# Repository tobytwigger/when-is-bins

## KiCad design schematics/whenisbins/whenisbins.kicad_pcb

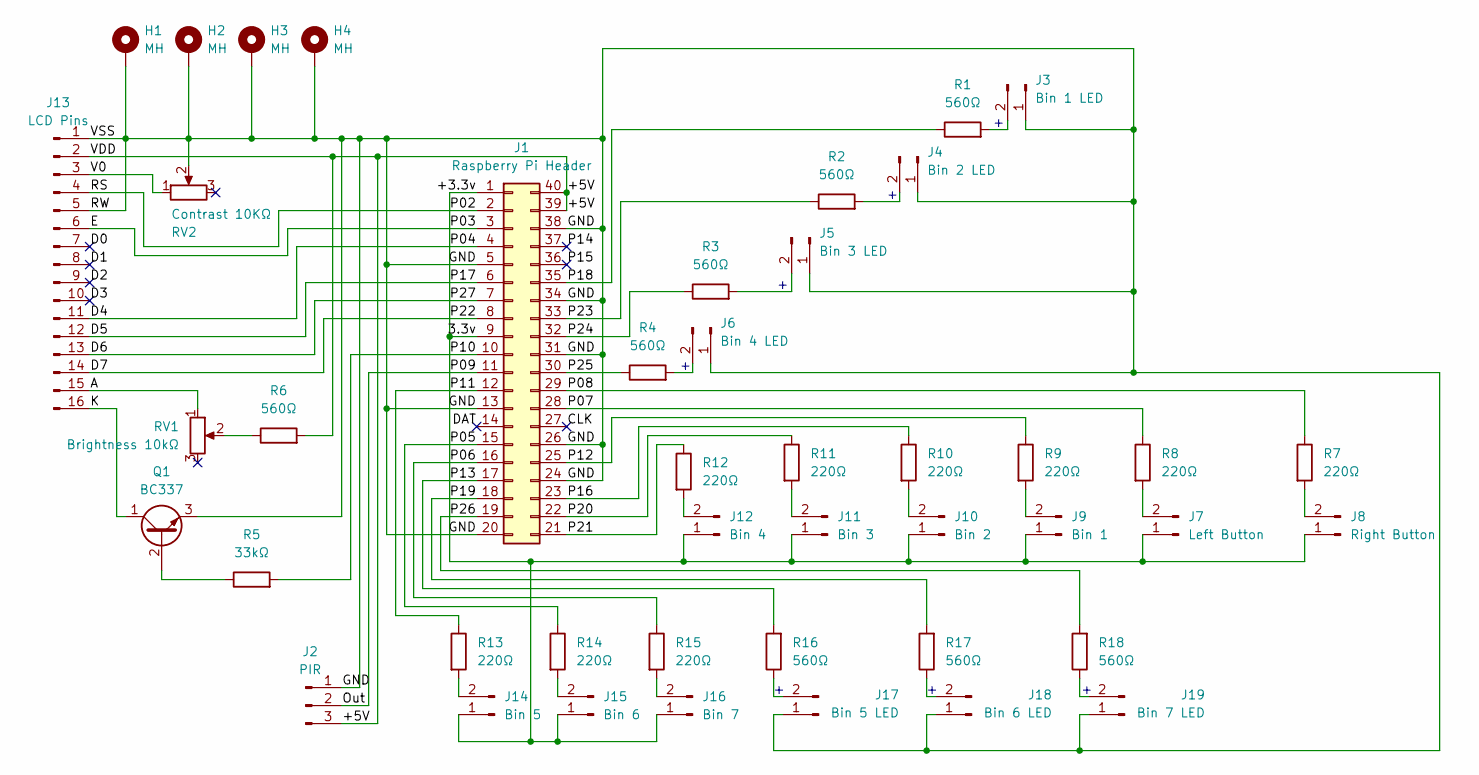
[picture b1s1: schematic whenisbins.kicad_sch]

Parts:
H1, H2, H3, H4: MH
J1: Raspberry Pi Header; PinHeader_2x20_P2.54mm_Vertical
J2: PIR; PinHeader_1x03_P2.54mm_Vertical
J3: Bin 1 LED; PinHeader_1x02_P2.54mm_Vertical
J4: Bin 2 LED; PinHeader_1x02_P2.54mm_Vertical
J5: Bin 3 LED; PinHeader_1x02_P2.54mm_Vertical
J6: Bin 4 LED; PinHeader_1x02_P2.54mm_Vertical
J7: Left Button; PinHeader_1x02_P2.54mm_Vertical
J8: Right Button; PinHeader_1x02_P2.54mm_Vertical
J9: Bin 1; PinHeader_1x02_P2.54mm_Vertical
J10: Bin 2; PinHeader_1x02_P2.54mm_Vertical
J11: Bin 3; PinHeader_1x02_P2.54mm_Vertical
J12: Bin 4; PinHeader_1x02_P2.54mm_Vertical
J13: LCD Pins; PinSocket_1x16_P2.54mm_Horizontal
J14: Bin 5; PinHeader_1x02_P2.54mm_Vertical
J15: Bin 6; PinHeader_1x02_P2.54mm_Vertical
J16: Bin 7; PinHeader_1x02_P2.54mm_Vertical
J17: Bin 5 LED; PinHeader_1x02_P2.54mm_Vertical
J18: Bin 6 LED; PinHeader_1x02_P2.54mm_Vertical
J19: Bin 7 LED; PinHeader_1x02_P2.54mm_Vertical
Q1: BC337; TO-92_Inline
R1, R2, R3, R4, R6, R16, R17, R18: 560Ω; R_Axial_DIN0207_L6.3mm_D2.5mm_P10.16mm_Horizontal
R5: 33kΩ; R_Axial_DIN0207_L6.3mm_D2.5mm_P10.16mm_Horizontal
R7, R8, R9, R10, R11, R12, R13, R14, R15: 220Ω; R_Axial_DIN0207_L6.3mm_D2.5mm_P10.16mm_Horizontal
RV1: Brightness 10kΩ; Potentiometer_Runtron_RM-065_Vertical
RV2: Contrast 10KΩ; Potentiometer_Runtron_RM-065_Vertical

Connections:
/+3.3v: J1.1, J1.9, J7.1, J8.1, J9.1, J10.1, J11.1, J12.1, J14.1, J15.1, J16.1
/+5V: J1.39, J1.40, J2.3, J13.2, R6.2
/A: J13.15, RV1.1
/CLK: J1.27
/D0: J13.7
/D1: J13.8
/D2: J13.9
/D3: J13.10
/D4: J1.4, J13.11
/D5: J1.6, J13.12
/D6: J1.7, J13.13
/D7: J1.8, J13.14
/DAT: J1.14
/E: J1.3, J13.6
/GND: H1.1, H2.1, H3.1, H4.1, J1.5, J1.13, J1.20, J1.24, J1.26, J1.31, J1.34, J1.38, J2.1, J3.1, J4.1, J5.1, J6.1, J13.1, J13.5, J17.1, J18.1, J19.1, Q1.3 (E), RV2.2
/K: J13.16, Q1.1 (C)
/Out: J1.11, J2.2
/P02: J1.2, J13.4
/P05: J1.15, R14.1
/P06: J1.16, R15.1
/P07: J1.28, R8.1
/P08: J1.29, R7.1
/P10: J1.10, R5.2
/P11: J1.12, R13.1
/P12: J1.25, R9.1
/P13: J1.17, R16.2
/P14: J1.37
/P15: J1.36
/P16: J1.23, R10.1
/P18: J1.35, R1.1
/P19: J1.18, R17.2
/P20: J1.22, R11.1
/P21: J1.21, R12.1
/P23: J1.33, R2.1
/P24: J1.32, R3.1
/P25: J1.30, R4.1
/P26: J1.19, R18.2
/V0: J13.3, RV2.1
unnamed: J3.2, R1.2
unnamed: J4.2, R2.2
unnamed: J5.2, R3.2
unnamed: J6.2, R4.2
unnamed: J7.2, R8.2
unnamed: J8.2, R7.2
unnamed: J9.2, R9.2
unnamed: J10.2, R10.2
unnamed: J11.2, R11.2
unnamed: J12.2, R12.2
unnamed: J14.2, R13.2
unnamed: J15.2, R14.2
unnamed: J16.2, R15.2
unnamed: J17.2, R16.1
unnamed: J18.2, R17.1
unnamed: J19.2, R18.1
unnamed: Q1.2 (B), R5.1
unnamed: R6.1, RV1.2

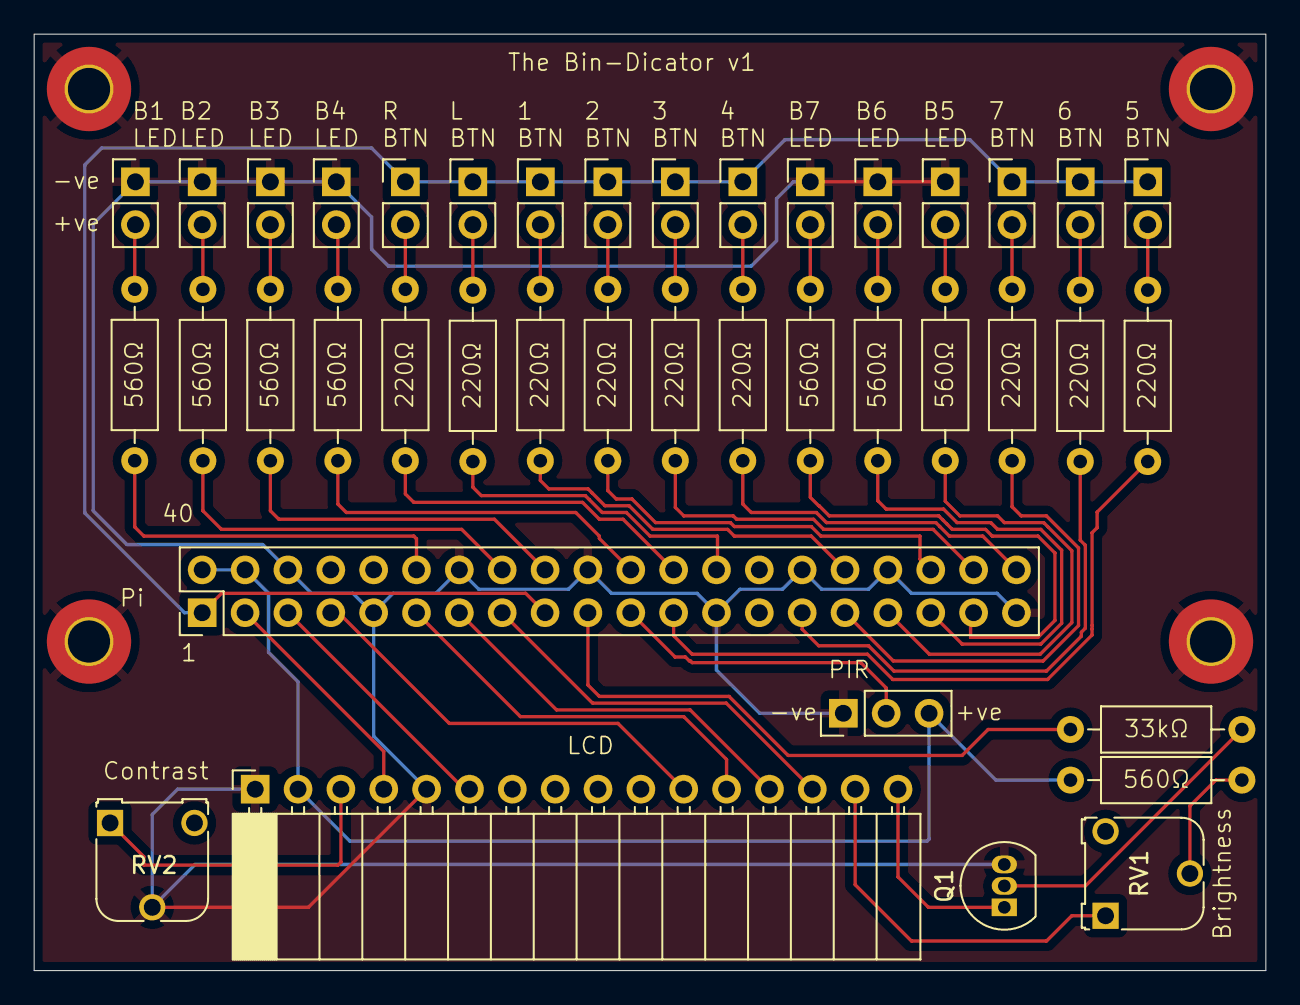
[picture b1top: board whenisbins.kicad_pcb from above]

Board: 2 copper layers, 73.0 x 55.5 mm, 44 parts (0 on the bottom side), 48 nets.

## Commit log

2025-01-06 Fixes
2025-01-07 Move database
2025-01-07 Possibly the final firmware fix
2025-01-07 Fix path used to the python script when called in node
2025-01-08 Rewrite app runner
2025-01-08 Boot on start up and config UI improvements
2025-01-09 Update PCB and electrical schematics and finalise pinouts
2025-01-09 Fix ui issue
2025-01-09 Support more councils
2025-01-09 Minor firmware updates
2025-01-10 Finalise pcb and set up selenium
2025-01-10 Add overridable bin days to js
2025-01-12 Add holiday schedules
2025-01-13 wip cleaning up routing
2025-01-13 Finish up new state management, add phasing to led driver, add scrolling to lcd driver and add bin out at settings
2025-01-13 Fix js
